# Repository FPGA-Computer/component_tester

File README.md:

Component tester

based on design from svn://mikrocontroller.net/transistortester/
Github: https://github.com/svn2github/transistortester

I made a few changes to the hardware for my own use:

- A boost mode power supply for operating from 1 AA NiMH battery at about 45mA.
  
- 16x2 characters LCD module with backlight High/low setting

- Power On/Off switch

- I/O mapping is based on Markus's version with the following exceptions:

  ATMega328 in TQFP with 2.5V reference at ADC6 and Battery voltage at ADC

  PC3 - PC5 are unused and are available on connector JP2

Project page:

https://hw-by-design.blogspot.com/2018/07/component-tester.html

Firmware: The files are from svn://mikrocontroller.net/transistortester/  
I only make a few minor changes to match my hardware.  They are included 
here for completeiness and I am not maintaining them.

Licensing:

Schematic: (in Eagle CAD) Creative Commons 4.0 Attribution 4.0 International

PCB & Layout: Creative Commons 4.0 Attribution 4.0 International

See https://creativecommons.org/licenses/by/4.0/

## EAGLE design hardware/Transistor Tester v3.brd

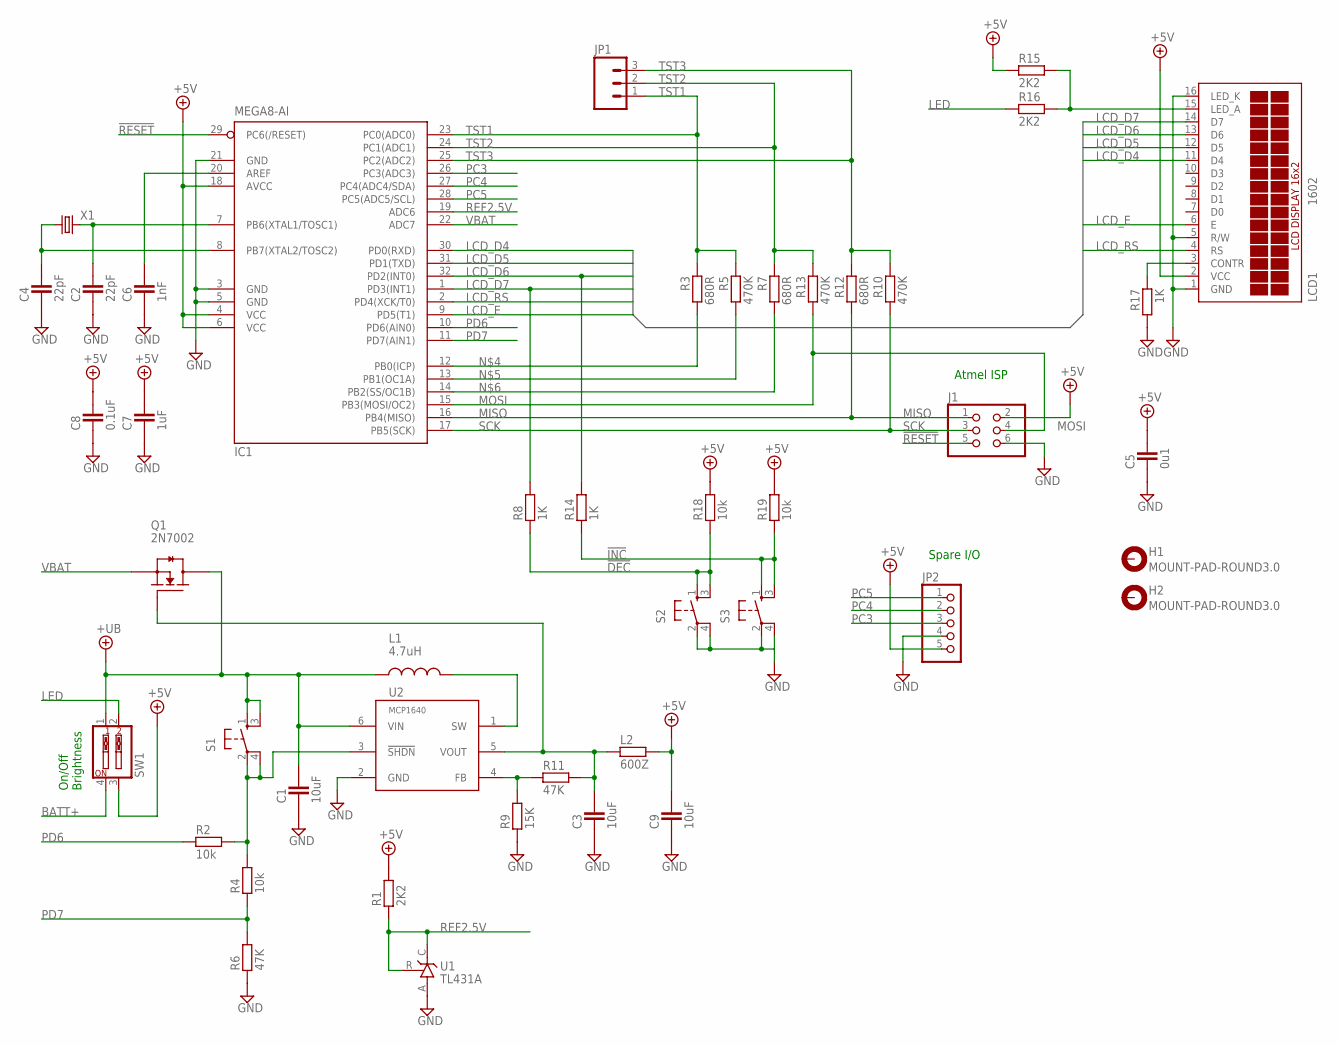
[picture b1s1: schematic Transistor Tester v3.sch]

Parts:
C1, C3, C9: 10uF; CAPC2012X145AN
C2, C4: 22pF; CAPC1608X92N
C5: 0u1; CAPC1608X92N
C6: 1nF; CAPC1608X92N
C7: 1uF; CAPC1608X92N
C8: 0.1uF; CAPC1608X92N
H1, H2: MOUNT-PAD-ROUND3.0; 3,0-PAD
IC1: MEGA8-AI; TQFP32-08
J1: PINHD-2X3_2.54; 2X03
JP1: M03POLAR; MOLEX-1X3
JP2: PINHD-1X5; 1X05
L1: 4.7uH; CD43
L2: 600Z; RESC2012X70N
LCD1: 1602; TUXGR_16X2_R2_NM
Q1: 2N7002; SOT95P280X135-3N
R1, R15, R16: 2K2; RESC1608X55N
R2, R4, R18, R19: 10k; RESC1608X55N
R3, R7, R12: 680R; RESC1608X55N
R5, R10, R13: 470K; RESC1608X55N
R6, R11: 47K; RESC1608X55N
R8, R14, R17: 1K; RESC1608X55N
R9: 15K; RESC1608X55N
S1, S2, S3: MOM_SWTH; MOM_SW
SW1: SW_DIP-2; EDG-02
U1: TL431A; TO92-CLP
U2: MCP1640; SOT26
X1: CRYSTALHC49UP; HC49UP

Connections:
!DEC: R8.1, R18.1, S2.1, S2.3 (2)
!INC: R14.1, R19.1, S3.1, S3.3 (2)
!RESET: IC1.29 (PC6(/RESET)), J1.5
!SHUTDN: R2.2, R4.2, S1.2 (3), S1.4, U2.3 (!SHDN)
+5V: C5.2, C7.2, C8.2, C9.2, IC1.4 (VCC), IC1.6 (VCC), IC1.18 (AVCC), J1.2, JP2.5, L2.2, LCD1.2 (VCC), R1.2, R15.1, R18.2, R19.2, SW1.3
+UB: C1.2, L1.1, Q1.3 (D), S1.1, S1.3 (2), SW1.1, U2.6 (VIN)
BATT+: SW1.4
GND: C1.1, C2.1, C3.1, C4.1, C5.1, C6.1, C7.1, C8.1, C9.1, IC1.3 (GND), IC1.5 (GND), IC1.21 (GND), J1.6, JP2.4, LCD1.1 (GND), LCD1.5 (R/W), LCD1.16 (LED_K), R6.1, R9.1, R17.2, S2.2 (3), S2.4, S3.2 (3), S3.4, U1.A, U2.2 (GND)
LCD_A: LCD1.15 (LED_A), R15.2, R16.2
LCD_D4: IC1.30 (PD0(RXD)), LCD1.11 (D4)
LCD_D5: IC1.31 (PD1(TXD)), LCD1.12 (D5)
LCD_D6: IC1.32 (PD2(INT0)), LCD1.13 (D6), R14.2
LCD_D7: IC1.1 (PD3(INT1)), LCD1.14 (D7), R8.2
LCD_E: IC1.9 (PD5(T1)), LCD1.6 (E)
LCD_RS: IC1.2 (PD4(XCK/T0)), LCD1.4 (RS)
LED: R16.1, SW1.2
MISO: IC1.16 (PB4(MISO)), J1.1, R12.2
MOSI: IC1.15 (PB3(MOSI/OC2)), J1.4, R13.2
unnamed: C4.2, IC1.8 (PB7(XTAL2/TOSC2)), X1.1
unnamed: L1.2, U2.1 (SW)
unnamed: C3.2, L2.1, Q1.1 (G), R11.2, U2.5 (VOUT)
unnamed: IC1.12 (PB0(ICP)), R3.2
unnamed: IC1.13 (PB1(OC1A)), R5.2
unnamed: IC1.14 (PB2(SS/OC1B)), R7.2
unnamed: R9.2, R11.1, U2.4 (FB)
unnamed: C2.2, IC1.7 (PB6(XTAL1/TOSC1)), X1.2
unnamed: C6.2, IC1.20 (AREF)
unnamed: LCD1.3 (CONTR), R17.1
PC3: IC1.26 (PC3(ADC3)), JP2.3
PC4: IC1.27 (PC4(ADC4/SDA)), JP2.2
PC5: IC1.28 (PC5(ADC5/SCL)), JP2.1
PD6: IC1.10 (PD6(AIN0)), R2.1
PD7: IC1.11 (PD7(AIN1)), R4.1, R6.2
REF2.5V: IC1.19 (ADC6), R1.1, U1.C, U1.R
SCK: IC1.17 (PB5(SCK)), J1.3, R10.2
TST1: IC1.23 (PC0(ADC0)), JP1.1, R3.1, R5.1
TST2: IC1.24 (PC1(ADC1)), JP1.2, R7.1, R13.1
TST3: IC1.25 (PC2(ADC2)), JP1.3, R10.1, R12.1
VBAT: IC1.22 (ADC7), Q1.2 (S)

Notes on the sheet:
Atmel ISP
Spare I/O
On/Off Brightness

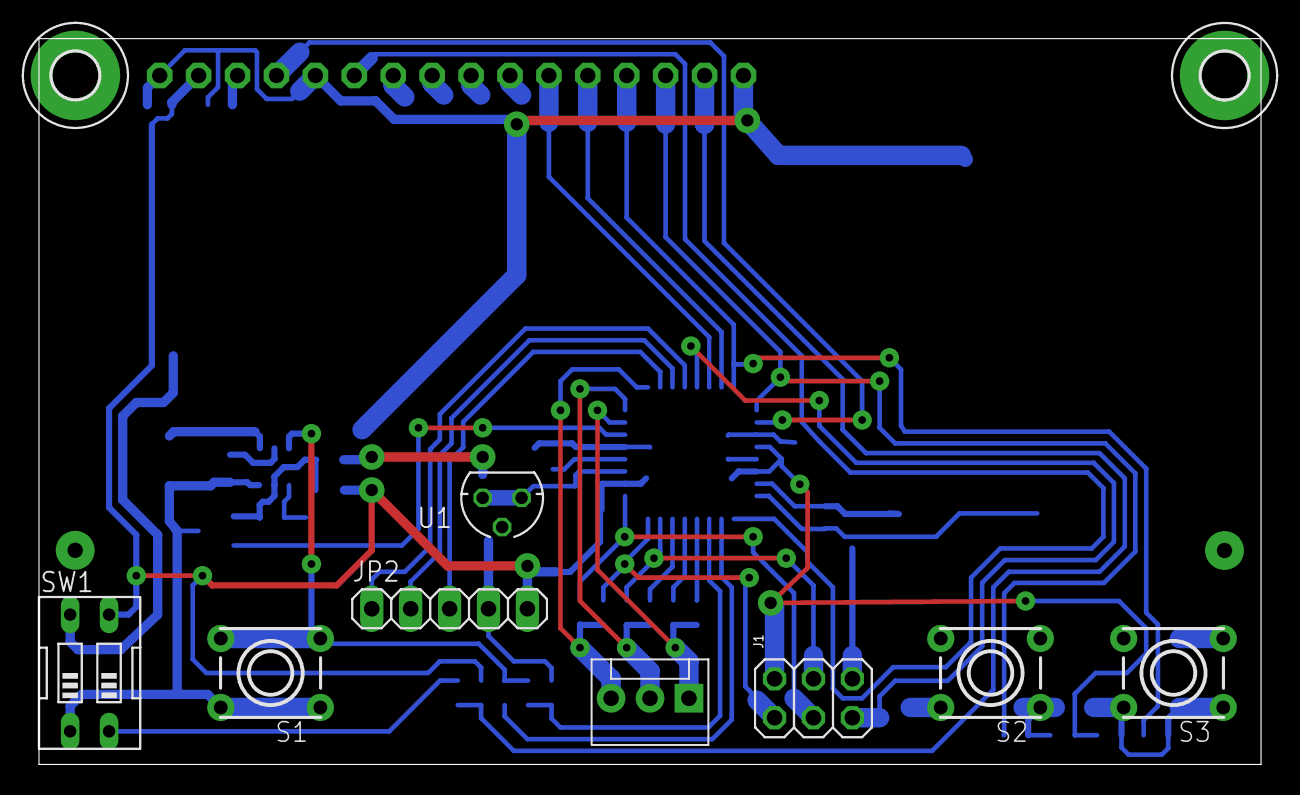
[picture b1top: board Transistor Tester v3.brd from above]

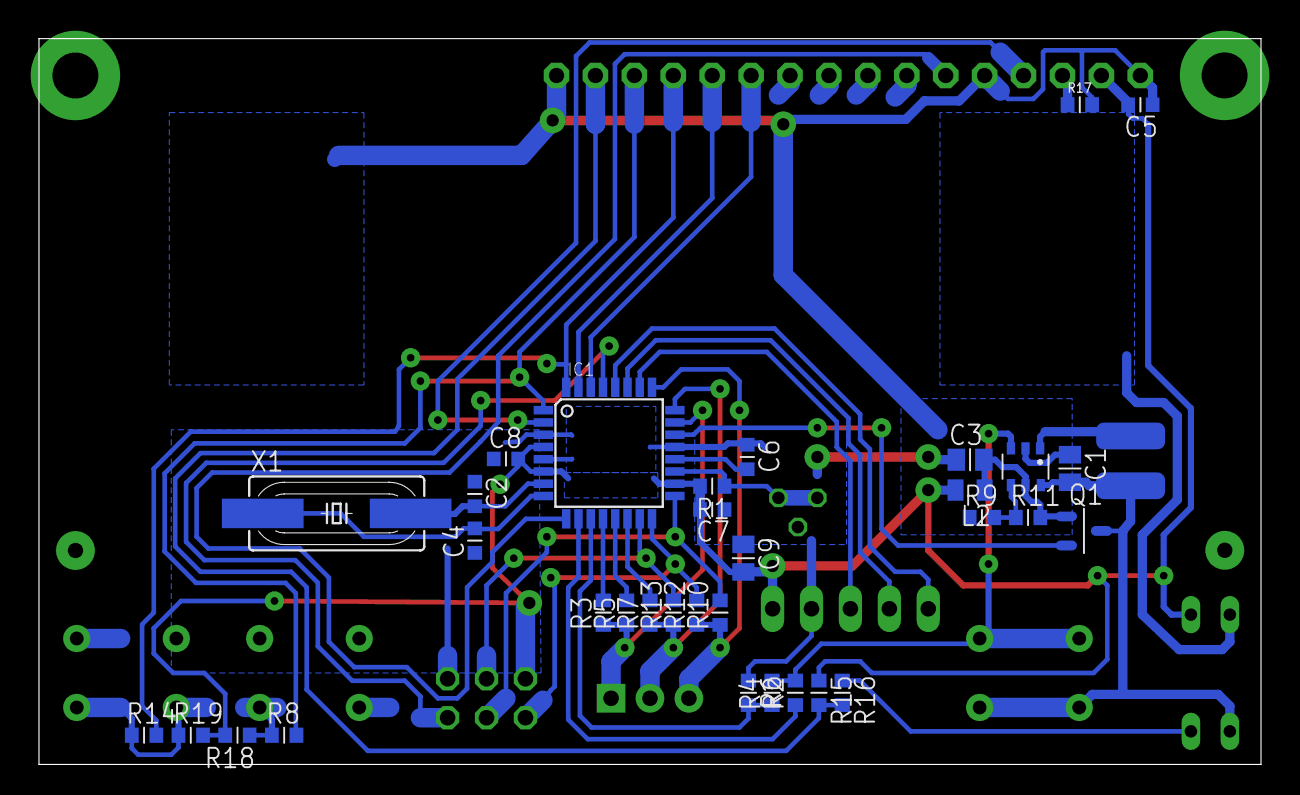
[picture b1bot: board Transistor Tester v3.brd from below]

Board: 2 copper layers, 79.8 x 47.4 mm, 45 parts (34 on the bottom side), 38 nets.

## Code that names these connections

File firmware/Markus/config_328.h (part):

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#define LCD_PORT         PORTD          /* port data register */
#define LCD_DDR          DDRD           /* port data direction register */
#define LCD_DB_STD                      /* use standard pins 0-3 for DB4-7 */
#define LCD_DB4          PD0            /* port pin used for DB4 */
#define LCD_DB5          PD1            /* port pin used for DB5 */
#define LCD_DB6          PD2            /* port pin used for DB6 */
#define LCD_DB7          PD3            /* port pin used for DB7 */
#define LCD_RS           PD4            /* port pin used for RS */
#define LCD_EN1          PD5            /* port pin used for E */
#define LCD_CHAR_X       16             /* characters per line */
#define LCD_CHAR_Y       2              /* number of lines */
#define FONT_HD44780_INT                /* internal 5x7 font: international */
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#define LCD_DB5          PCF8574_P5     /* port pin used for DB5 */
#define LCD_DB6          PCF8574_P6     /* port pin used for DB6 */
#define LCD_DB7          PCF8574_P7     /* port pin used for DB7 */
#define LCD_RS           PCF8574_P0     /* port pin used for RS */
#define LCD_RW           PCF8574_P1     /* port pin used for RW */
#define LCD_EN1          PCF8574_P2     /* port pin used for E */
#define LCD_LED          PCF8574_P3     /* port pin used for backlight */
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#define I2C_PORT         PORTD          /* I2C port data register */
#define I2C_DDR          DDRD           /* I2C port data direction register */
#define I2C_PIN          PIND           /* I2C port input pins register */
#define I2C_SDA          PD0            /* port pin used for SDA */
#define I2C_SCL          PD1            /* port pin used for SCL */
#endif


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/*
 *  ST7565R, SPI interface (bit-bang)
 *  - settings for Electronic Assembly EA DOGM/DOGL128-6
 *  - uses LCD_CS to support rotary encoder in parallel at PD2/3
 */

#if 0
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#define LCD_SPI                         /* SPI interface */
#define LCD_PORT         PORTD          /* port data register */
#define LCD_DDR          DDRD           /* port data direction register */
#define LCD_RESET        PD0            /* port pin used for /RES (optional) */
#define LCD_CS           PD5            /* port pin used for /CS1 (optional) */
#define LCD_A0           PD1            /* port pin used for A0 */
#define LCD_SCL          PD2            /* port pin used for SCL */
#define LCD_SI           PD3            /* port pin used for SI (LCD's data input) */
#define LCD_DOTS_X       128            /* number of horizontal dots */
#define LCD_DOTS_Y       64             /* number of vertical dots */
//#define LCD_FLIP_X                      /* enable horizontal flip */
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#define LCD_SPI                         /* SPI interface */
#define LCD_PORT         PORTD          /* port data register */
#define LCD_DDR          DDRD           /* port data direction register */
#define LCD_RES          PD4            /* port pin used for /RES (optional) */
#define LCD_CS           PD5            /* port pin used for /CS (optional) */
#define LCD_DC           PD3            /* port pin used for D/C */
#define LCD_SCK          PD2            /* port pin used for SCK */
#define LCD_SDI          PD1            /* port pin used for SDI (LCD's data input) */
//#define LCD_SDO          PD0            /* port pin used for SDO (LCD's data output) */
#define LCD_DOTS_X       320            /* number of horizontal dots */
#define LCD_DOTS_Y       240            /* number of vertical dots */
//#define LCD_FLIP_X                      /* enable horizontal flip */
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#define LCD_SPI                         /* SPI interface */
#define LCD_PORT         PORTD          /* port data register */
#define LCD_DDR          DDRD           /* port data direction register */
#define LCD_RES          PD4            /* port pin used for /RESX (optional) */
#define LCD_CS           PD5            /* port pin used for /CSX (optional) */
#define LCD_DC           PD3            /* port pin used for D/CX */
#define LCD_SCL          PD2            /* port pin used for SCL */
#define LCD_SDA          PD1            /* port pin used for SDA */
#define LCD_DOTS_X       128            /* number of horizontal dots */
#define LCD_DOTS_Y       160            /* number of vertical dots */
//#define LCD_FLIP_X                      /* enable horizontal flip */
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#define LCD_SPI                         /* SPI interface */
#define LCD_PORT         PORTD          /* port data register */
#define LCD_DDR          DDRD           /* port data direction register */
#define LCD_RES          PD4            /* port pin used for /RES (optional) */
#define LCD_SCE          PD5            /* port pin used for /SCE (optional) */
#define LCD_DC           PD3            /* port pin used for D/C */
#define LCD_SCLK         PD2            /* port pin used for SCLK */
#define LCD_SDIN         PD1            /* port pin used for SDIN (LCD's data input) */
#define LCD_DOTS_X       84             /* number of horizontal dots */
#define LCD_DOTS_Y       48             /* number of vertical dots */
#define LCD_CONTRAST     66             /* default contrast (1-127) */
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#define LCD_SPI                         /* SPI interface */
#define LCD_PORT         PORTD          /* port data register */
#define LCD_DDR          DDRD           /* port data direction register */
#define LCD_RESET        PD4            /* port pin used for /RESET (optional) */
#define LCD_CS           PD5            /* port pin used for CS (optional) */
#define LCD_SCLK         PD2            /* port pin used for SCLK */
#define LCD_SID          PD1            /* port pin used for SID (LCD's data input) */
#define LCD_DOTS_X       128            /* number of horizontal dots */
#define LCD_DOTS_Y       64             /* number of vertical dots */
#define FONT_8X8_H                      /* 8x8 font, horizonally aligned */
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#define LCD_PORT         PORTD          /* port data register */
#define LCD_DDR          DDRD           /* port data direction register */
#define LCD_DB_STD                      /* use standard pins 0-3 for DB4-7 */
#define LCD_DB4          PD0            /* port pin used for DB4 */
#define LCD_DB5          PD1            /* port pin used for DB5 */
#define LCD_DB6          PD2            /* port pin used for DB6 */
#define LCD_DB7          PD3            /* port pin used for DB7 */
#define LCD_RS           PD4            /* port pin used for RS */
#define LCD_EN           PD5            /* port pin used for E */
#define LCD_DOTS_X       128            /* number of horizontal dots */
#define LCD_DOTS_Y       64             /* number of vertical dots */
#define FONT_8X8_H                      /* 8x8 font, horizonally aligned */
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#define LCD_SPI                         /* SPI interface */
#define LCD_PORT         PORTD          /* port data register */
#define LCD_DDR          DDRD           /* port data direction register */
#define LCD_RES          PD4            /* port pin used for /RESX (optional) */
#define LCD_CS           PD5            /* port pin used for /CSX (optional) */
#define LCD_DC           PD3            /* port pin used for D/CX */
#define LCD_SCL          PD2            /* port pin used for SCL */
#define LCD_SDA          PD1            /* port pin used for SDA/SDIO */
#define LCD_DOTS_X       128            /* number of horizontal dots */
#define LCD_DOTS_Y       128            /* number of vertical dots */
#define LCD_OFFSET_X      32            /* x offset of 32 dots (160-128) */
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#define LCD_SPI                         /* SPI interface */
#define LCD_PORT         PORTD          /* port data register */
#define LCD_DDR          DDRD           /* port data direction register */
#define LCD_RESET        PD4            /* port pin used for /RES (optional) */
#define LCD_CS           PD5            /* port pin used for /CS (optional) */
#define LCD_DC           PD3            /* port pin used for D/C */
#define LCD_SCLK         PD2            /* port pin used for SCLK */
#define LCD_SDIN         PD1            /* port pin used for SDIN (LCD's data input) */
#define LCD_DOTS_X       128            /* number of horizontal dots */
#define LCD_DOTS_Y       64             /* number of vertical dots */
#define LCD_FLIP_X                      /* enable horizontal flip */
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#define LCD_I2C_ADDR     0x3c           /* SSD1306's I2C address */
#define LCD_PORT         PORTD          /* port data register */
#define LCD_DDR          DDRD           /* port data direction register */
#define LCD_RESET        PD4            /* port pin used for /RES (optional) */
#define LCD_DOTS_X       128            /* number of horizontal dots */
#define LCD_DOTS_Y       64             /* number of vertical dots */
#define LCD_FLIP_X                      /* enable horizontal flip */
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#define I2C_PORT         PORTD          /* I2C port data register */
#define I2C_DDR          DDRD           /* I2C port data direction register */
#define I2C_PIN          PIND           /* I2C port input pins register */
#define I2C_SDA          PD0            /* port pin used for SDA */
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
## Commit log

2018-11-11 added files

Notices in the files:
firmware/Markus/config_328.h:
(c) 2012-2017 by Markus Reschke
parts and their libraries:
SparkFun-Connectors: Licensing: Creative Commons ShareAlike 4.0 International - https://creativecommons.org/licenses/by-sa/4.0
